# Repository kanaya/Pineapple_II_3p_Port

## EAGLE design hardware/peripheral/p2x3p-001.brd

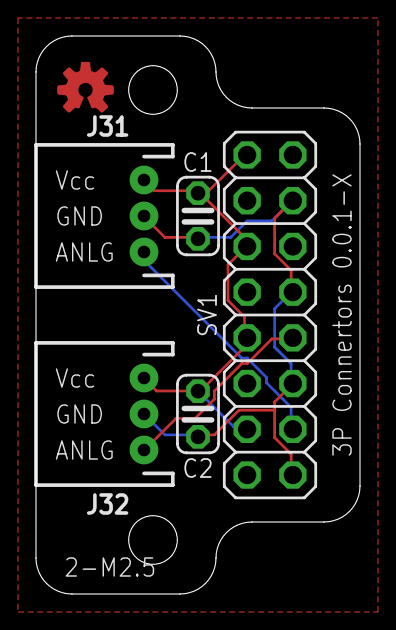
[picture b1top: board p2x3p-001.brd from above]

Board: 2 copper layers, 18.0 x 31.0 mm, 7 parts (1 on the bottom side), 4 nets.

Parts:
C1, C2: C025-024X044
J31, J32: JST-3-PTH
LOGO1: OSHW-LOGOS-COPPER; OSHW-LOGO-S_COPPER
SV1: 2X08
U$1: PINEAPPLE450_SILK

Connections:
ANLG0: J31.1, SV1.3
ANLG1: J32.1, SV1.7
GND: C1.2, C2.2, J31.2, J32.2, SV1.1, SV1.5, SV1.9, SV1.13
VCC: C1.1, C2.1, J31.3, J32.3, SV1.4, SV1.8, SV1.12, SV1.16

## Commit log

2022-08-16 Imported from RLY Port 0.0.2-X.
2022-08-17 Imported (again) from Hex Sw 0.0.2-X.
2022-08-17 WIP.
2022-08-17 GND pattern.
2022-08-17 Silk.
2022-08-29 Just changed view.

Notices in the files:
parts and their libraries:
SparkFun-Aesthetics: Licensing: Creative Commons ShareAlike 4.0 International - https://creativecommons.org/licenses/by-sa/4.0
